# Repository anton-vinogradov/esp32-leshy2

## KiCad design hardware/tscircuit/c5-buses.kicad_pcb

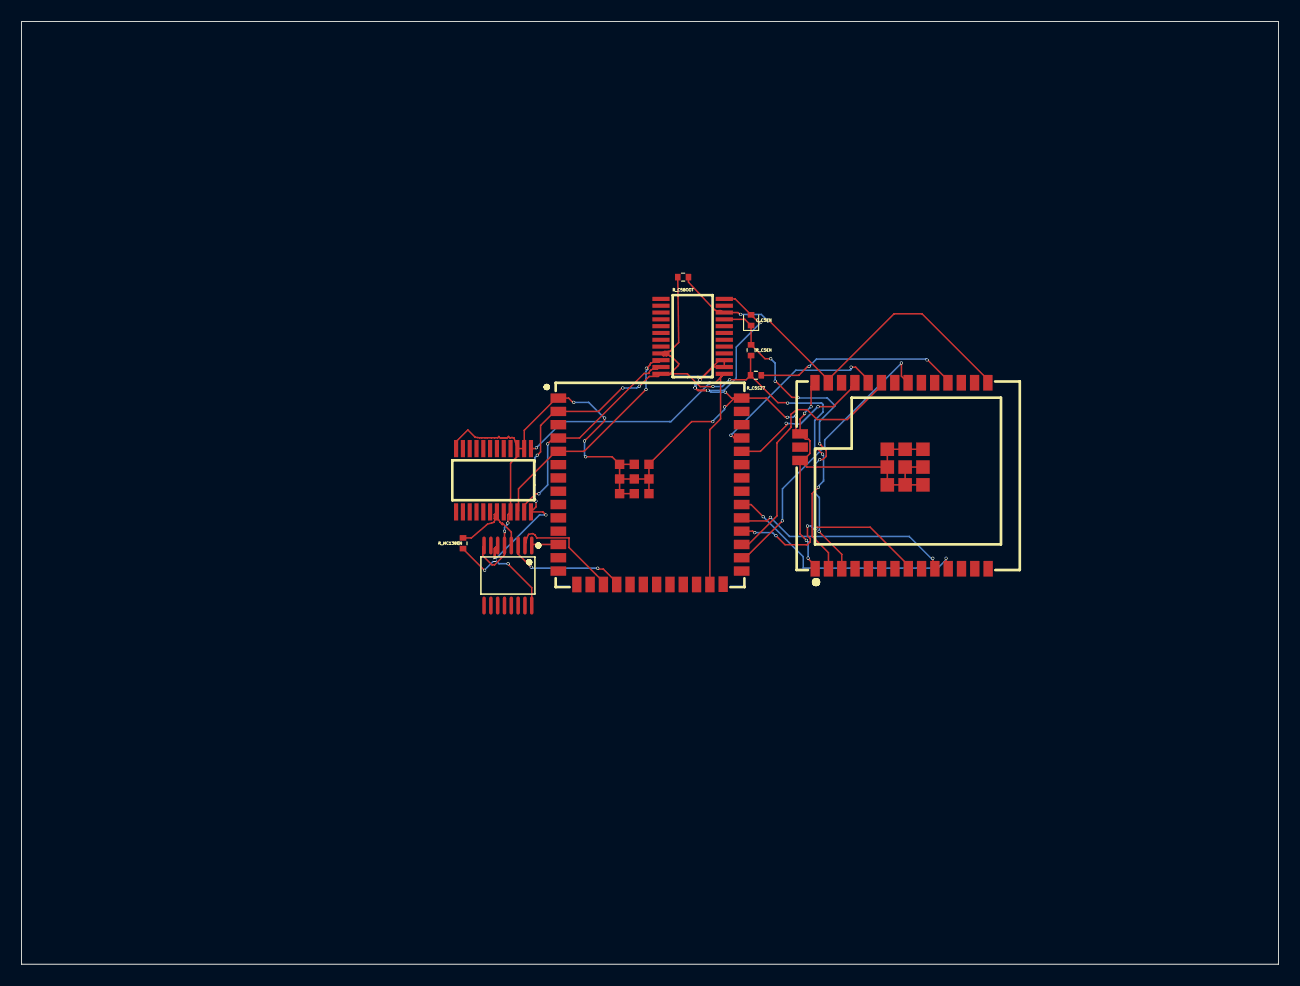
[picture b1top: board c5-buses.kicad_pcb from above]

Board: 2 copper layers, 120.0 x 90.0 mm, 10 parts (0 on the bottom side), 19 nets.

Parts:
C_C5EN: 1uF; capacitor_cap0402
R_C5BOOT, R_C5EN, R_C5S27: 10kΩ; resistor_res0402
R_HC138EN: 10kΩ; resistor_res0402
U10, U11, U12, U13, U20: chip

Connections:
.U20 > .IO27 to .R_C5S27 > .pin1: R_C5S27.1, U20.18
C5LINK_CS: U10.31, U20.10
C5LINK_DRDY: U10.32, U20.11
C5LINK_MISO: U10.30, U20.8
C5LINK_MOSI: U10.29, U20.23
C5LINK_SCK: U10.28, U20.21
C5_BOOT: R_C5BOOT.1, U13.10, U20.15, U20.27
C5_EN: C_C5EN.1, R_C5EN.1, U13.9, U20.3
C5_FLASH_RX: U10.36, U20.25
C5_FLASH_TX: U10.37, U20.24
GND: C_C5EN.2, U10.1, U10.40, U10.41, U10.42, U10.43, U10.44, U10.45, U10.46, U10.47, U10.48, U10.49, U11.5, U11.8, U12.2, U12.3, U12.12, U12.21, U13.2, U13.3, U13.12, U20.1, U20.28, U20.29, U20.30, U20.32, U20.33, U20.34, U20.35, U20.36, U20.37, U20.38, U20.39, U20.40
HC138_A: U10.12, U11.1
HC138_B: U10.17, U11.2
HC138_C: U10.18, U11.3
HC138_EN: R_HC138EN.1, U11.4, U12.19
I2C_SCL: U10.5, U12.22, U13.22
I2C_SDA: U10.4, U12.23, U13.23
PCA9555_INT: U10.25, U12.1, U13.1
V3V3: R_C5BOOT.2, R_C5EN.2, R_C5S27.2, R_HC138EN.2, U10.2, U11.6, U11.16, U12.24, U13.21, U13.24, U20.2
